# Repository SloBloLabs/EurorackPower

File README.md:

# EurorackPower

A(nother) power distribution board, mainly intended to learn about the PCB design an manufacturing process.

Here is the [BOM] with mouser references.

## Features

 * Using 1,4mm traces, enough to process 3A on 1oz PCB
 * Additional capacitors on board per power line to counter ripple and noise
 * Onboard jumper to normalize 0V to earth ground
 * Dashed silkscreen lines to safely cut the PCB if less than 3 rows/connectors are actually needed for the application
 * Open Source Hardware

## Images

## Additional Info

This open hardware project needs an external +12V, 0V, -12V power supply.

Please find the [Wiring] schematic for further details.

Watch the related [video] on Youtube for an in depth tutorial.

[BOM]: EurorackPowerBOM_2019-03-02.xlsx
[Wiring]: KiCad/Wiring/Wiring.pdf
[video]: https://youtu.be/7tzhh7atj4o

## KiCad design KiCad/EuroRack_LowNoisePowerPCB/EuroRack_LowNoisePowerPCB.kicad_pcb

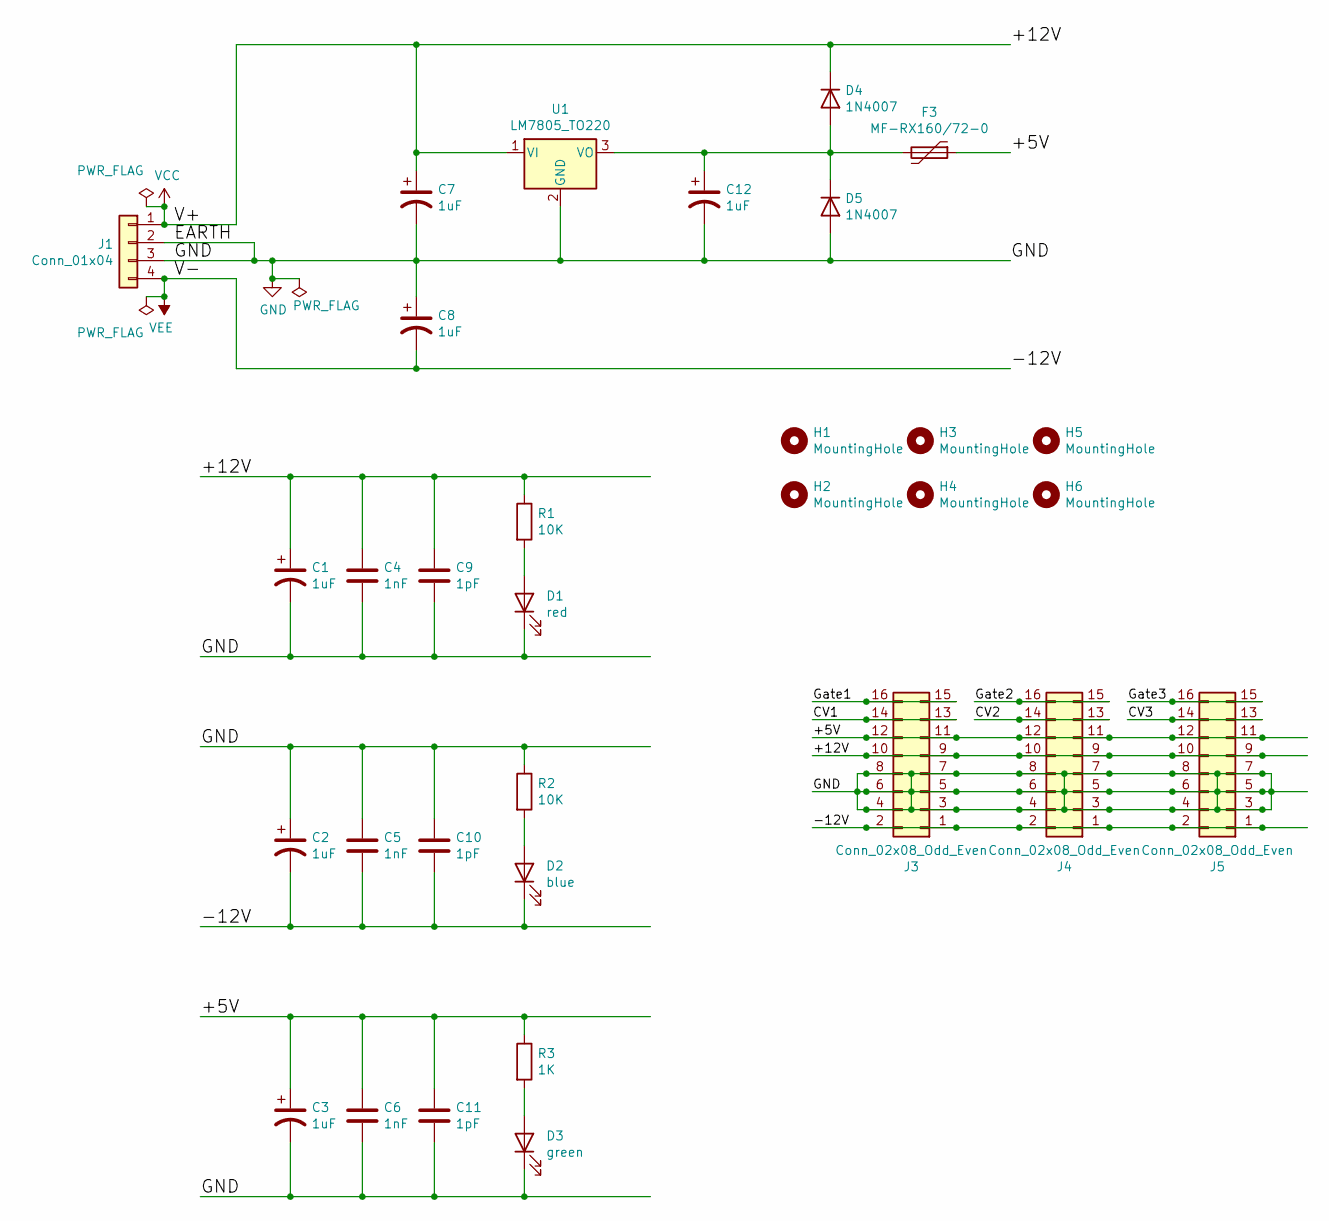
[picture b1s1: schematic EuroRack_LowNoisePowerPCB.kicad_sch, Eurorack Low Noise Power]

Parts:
C1, C2, C3, C7, C8, C12: 1uF; CP_Radial_D5.0mm_P2.00mm
C4, C5, C6: 1nF; C_Disc_D5.0mm_W2.5mm_P2.50mm
C9, C10, C11: 1pF; C_Disc_D5.0mm_W2.5mm_P2.50mm
D1: red; LED_D5.0mm
D2: blue; LED_D5.0mm
D3: green; LED_D5.0mm
D4, D5: 1N4007; D_DO-34_SOD68_P7.62mm_Horizontal
F3: MF-RX160/72-0; Fuse_Bourns_MF-RG900
H1, H2, H3, H4, H5, H6: MountingHole; MountingHole_4.3mm_M4
J1: Conn_01x04; PhoenixContact_MSTBA_2,5_4-G-5,08_1x04_P5.08mm_Horizontal
J3, J4, J5: Conn_02x08_Odd_Even; IDC-Header_2x08_P2.54mm_Vertical
R1, R2: 10K; R_Axial_DIN0207_L6.3mm_D2.5mm_P7.62mm_Horizontal
R3: 1K; R_Axial_DIN0207_L6.3mm_D2.5mm_P7.62mm_Horizontal
U1: LM7805_TO220; TO-220-3_Vertical

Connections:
/+5V: C3.1, C6.1, C11.1, F3.1, J3.11, J3.12, J4.11, J4.12, J5.11, J5.12, R3.1
/CV1: J3.13, J3.14
/CV2: J4.13, J4.14
/CV3: J5.13, J5.14
/Gate1: J3.15, J3.16
/Gate2: J4.15, J4.16
/Gate3: J5.15, J5.16
GND: C1.2, C2.1, C3.2, C4.2, C5.1, C6.2, C7.2, C8.1, C9.2, C10.1, C11.2, C12.2, D1.1 (K), D3.1 (K), D5.2 (A), J1.2, J1.3, J3.3, J3.4, J3.5, J3.6, J3.7, J3.8, J4.3, J4.4, J4.5, J4.6, J4.7, J4.8, J5.3, J5.4, J5.5, J5.6, J5.7, J5.8, R2.1, U1.2 (GND)
unnamed: D1.2 (A), R1.2
unnamed: D2.2 (A), R2.2
unnamed: D3.2 (A), R3.2
unnamed: C12.1, D4.2 (A), D5.1 (K), F3.2, U1.3 (VO)
VCC: C1.1, C4.1, C7.1, C9.1, D4.1 (K), J1.1, J3.9, J3.10, J4.9, J4.10, J5.9, J5.10, R1.1, U1.1 (VI)
VEE: C2.2, C5.2, C8.2, C10.2, D2.1 (K), J1.4, J3.1, J3.2, J4.1, J4.2, J5.1, J5.2

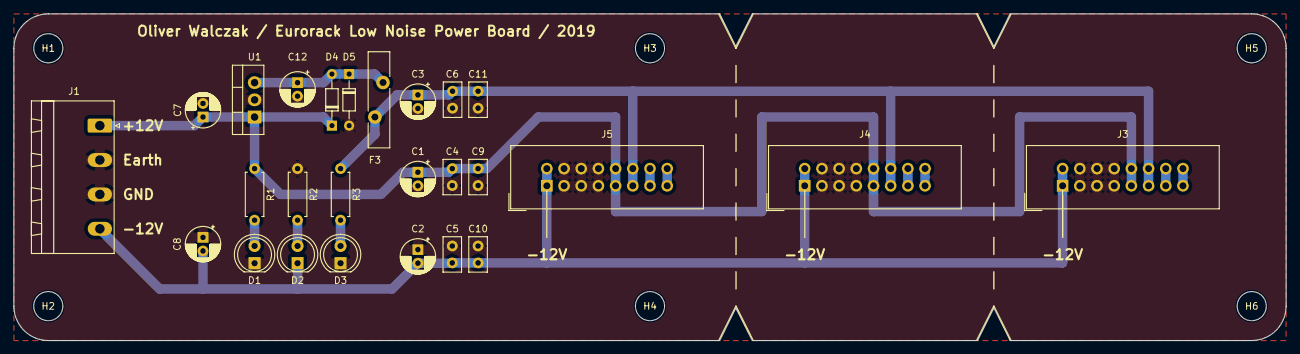
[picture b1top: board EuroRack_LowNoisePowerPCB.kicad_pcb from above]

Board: 2 copper layers, 188.0 x 48.3 mm, 32 parts (0 on the bottom side), 14 nets.

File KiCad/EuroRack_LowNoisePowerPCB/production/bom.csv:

Designator,Footprint,Quantity,Value,LCSC Part #
"C1, C12, C2, C3, C7, C8",CP_Radial_D5.0mm_P2.00mm,6,1uF,
"C10, C11, C9",C_Disc_D5.0mm_W2.5mm_P2.50mm,3,1pF,
"C4, C5, C6",C_Disc_D5.0mm_W2.5mm_P2.50mm,3,1nF,
D1,LED_D5.0mm,1,red,
D2,LED_D5.0mm,1,blue,
D3,LED_D5.0mm,1,green,
"D4, D5",D_DO-34_SOD68_P7.62mm_Horizontal,2,1N4007,
F3,Fuse_Bourns_MF-RG900,1,MF-RX160/72-0,
"H1, H2, H3, H4, H5, H6",MountingHole_4.3mm_M4,6,MountingHole,
J1,"PhoenixContact_MSTBA_2,5_4-G-5,08_1x04_P5.08mm_Horizontal",1,Conn_01x04,
"J3, J4, J5",IDC-Header_2x08_P2.54mm_Vertical,3,Conn_02x08_Odd_Even,
"R1, R2",R_Axial_DIN0207_L6.3mm_D2.5mm_P7.62mm_Horizontal,2,10K,
R3,R_Axial_DIN0207_L6.3mm_D2.5mm_P7.62mm_Horizontal,1,1K,
U1,TO-220-3_Vertical,1,LM7805_TO220,

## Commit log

2019-03-01 initial upload of KiCad Low Noice Power PCD
2019-03-01 Add wiring schematic
2019-03-01 Move wiring schematic to KiCad folder
2019-03-01 Rearrangement of wiring subfolders
2019-03-10 Screenshots added BOM updated Readme updated
2019-03-12 Add video icon
2023-11-26 Migrate to KiCad 7 Remove PTC and remove grounding option
